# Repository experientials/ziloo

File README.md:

# Ziloo

Ziloo is an independent device that sees and senses the environment. It recognises objects and behavior based on what it has been taught. It outputs an event log describing what is perceived.
Ziloo can be placed on a shelf, wall or embedded. I will recognise things and people it has been trained to recognise. They have to appear in front within 20cm - 200cm. Ziloo is primarily used indoors and used at all times of the day.

It receives stereo video input over 2 x 2-lane MIPI CSI2. Additionally it receives sensor input over I2C
for distance, color, brightness. The sensor inputs are processed and disected to identify objects, people and
behaviour. Ziloo can connect over USB to make the output available.

Ziloo will be launched on Kickstarter in 2022.

TODO 3D Exploded assembly
https://www.fiverr.com/visual_pro022/3d-product-animation-3d-product-video-3d-animation-3d-product-animation?context_referrer=search_gigs&source=top-bar&ref_ctx_id=ea6e5c3e42e5d61ed2beb57da5dea006&pckg_id=1&pos=13&context_type=auto&funnel=ea6e5c3e42e5d61ed2beb57da5dea006

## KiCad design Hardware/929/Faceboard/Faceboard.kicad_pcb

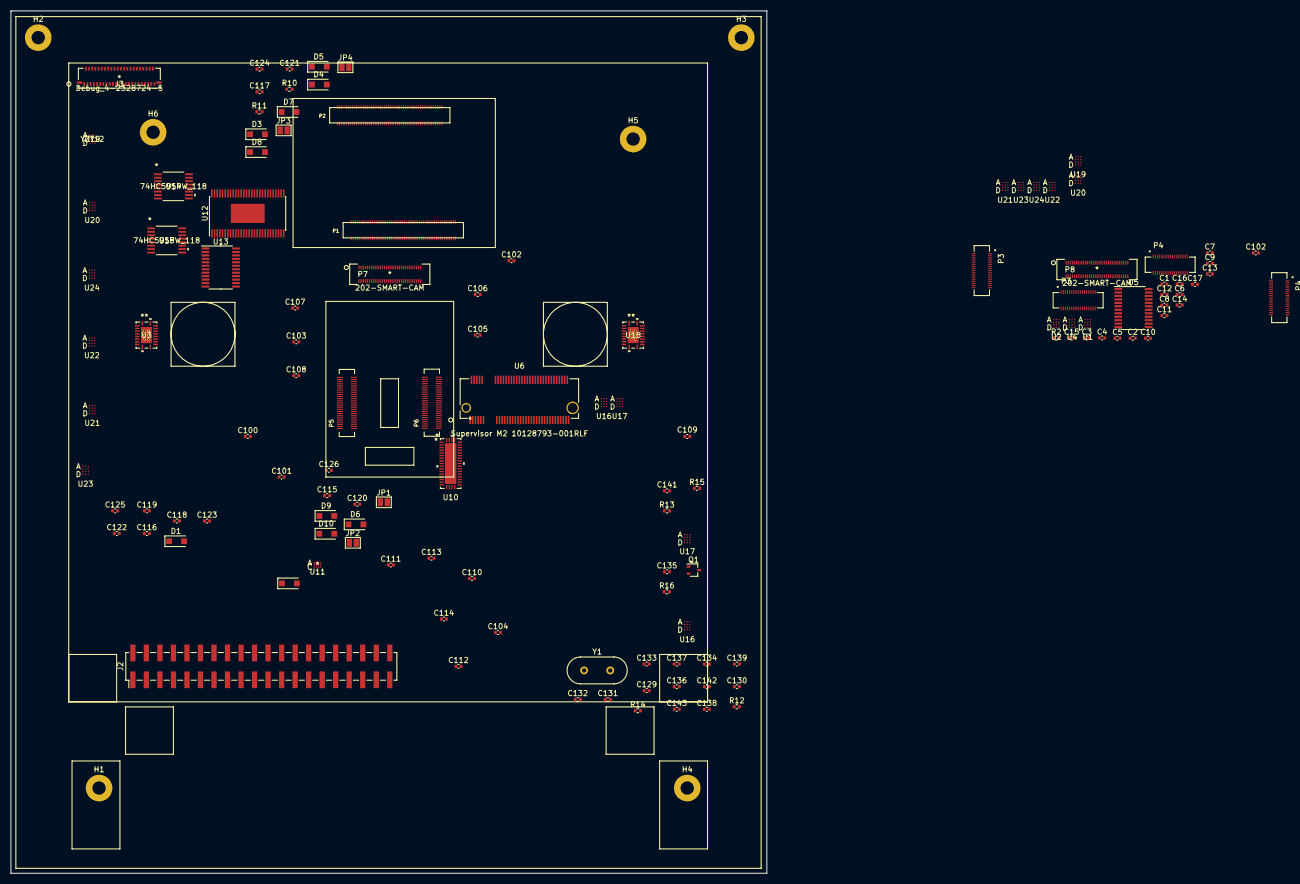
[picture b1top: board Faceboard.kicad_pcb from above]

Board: 4 copper layers, 142.0 x 162.0 mm, 130 parts (0 on the bottom side), 161 nets, no tracks yet.

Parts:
C1, C2, C6, C116, C121: 1uF; C_0402_1005Metric
C3, C4, C5, C7, C8, C9, C10, C11, C12, C13, C14, C15, C16, C17, C101, C102, C102#2, C103, C104, C105, C106, C107, C108, C109, C110, C111, C112, C113, C114, C115, C117, C118, C119, C120, C122, C123, C124, C125, C133, C134, C141, C142: 100nF; C_0402_1005Metric
C100: 10nF; C_0402_1005Metric
C126: CAP; C_0402_1005Metric
C129, C143: 27pF; C_0402_1005Metric
C130, C131, C137, C138, C139: 100uF; C_0402_1005Metric
C132, C136: 10uF; C_0402_1005Metric
C135: 100pF; C_0402_1005Metric
D1, D2, D3, D4, D5, D6, D7, D8, D9, D10: D_Schottky; D_SOD-123F
H1, H2, H3, H4, H5, H6: MountingHole; MountingHole_2.5mm_Pad
J2: Raspberry_Pi_to_Ziloo; PinHeader_2x20_P2.54mm_Vertical_SMD
J3: Debug_4-2328724-5; 4-2328724-5
JP1: TDO; SolderJumper-2_P1.3mm_Open_Pad1.0x1.5mm
JP2: TDI; SolderJumper-2_P1.3mm_Open_Pad1.0x1.5mm
JP3: SYS_SDA; SolderJumper-2_P1.3mm_Open_Pad1.0x1.5mm
JP4: SYS_SCL; SolderJumper-2_P1.3mm_Open_Pad1.0x1.5mm
P1: UCM-P1-100DS-0.4V; HRS_DF40C-100DS-0.4V(51)
P2: UCM-P2-100DS-0.4V; HRS_DF40C-100DS-0.4V(51)
P3, P3#2, P4, P4#2: 201-SOCKET-34DS-0.4V(51); HIROSE_DF40C-34DS-0.4V(51)
P5: T-USB_PWRCTL-50; HRS_DF40C-50DS-0.4V(51)
P6: T-USB_HIGH-SPEED-50; HRS_DF40C-50DS-0.4V(51)
P7, P8: 202-SMART-CAM; DF40C-60DS-0.4V51
Q1: 2SC4213; SOT-323_SC-70
R2, R10: 10K; R_0402_1005Metric
R11: R; R_0402_1005Metric
R12: 10k; R_0402_1005Metric
R13: 1k; R_0402_1005Metric
R14: 100K; R_0402_1005Metric
R15, R16: 4.7K; R_0402_1005Metric
U1, U2, U4, U16#2, U17, U19, U20#2, U21#2, U22#2, U23, U24: TXS0104; TXS0104EYZTR
U3, U18: SN74CB3Q3245RGYR
U5, U13: PCA9555PW; TSSOP-24_4.4x7.8mm_P0.65mm
U6: Supervisor M2 10128793-001RLF; 10128793-001RLF
U10: CBTL04083ABS_518
U11: TS5USBC410YFFR
U12: Faceboard_Expander_FR2032IG56; HTSSOP-56-1EP_6.1x14mm_P0.5mm_EP3.61x6.35mm
U14, U15: 74HC595PW_118; TSSOP-16
U16, U17#2, U19#2, U20, U21, U22, U23#2, U24#2: YZT12; TXS0104EYZTR
Y1: 25.000MHz; Crystal_HC18-U_Vertical

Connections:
+1V8: C9.1, C13.1, C15.1, C103.1, C105.1, C107.1, C109.1, C111.1, C113.1, C133.1, C141.1, P3.4 (VCC_1V8), P3#2.4 (VCC_1V8), P4.4 (VCC_1V8), P4#2.4 (VCC_1V8), P7.12 (1V8), P7.30 (1V8), U1.B1 (VCCB), U2.B1 (VCCB), U4.B1 (VCCB), U16#2.B1 (VCCB), U17.B1 (VCCB), U19.B1 (VCCB), U20#2.B1 (VCCB), U21#2.B1 (VCCB), U22#2.B1 (VCCB), U23.B1 (VCCB), U24.B1 (VCCB)
+2V8: P3.2 (AVDD_2V8), P3#2.2 (AVDD_2V8), P4.2 (AVDD_2V8), P4#2.2 (AVDD_2V8)
+3.3V: C1.2, C2.2, C3.2, C4.2, C5.2, C11.1, C14.1, C16.1, C17.2, C104.1, C106.1, C108.1, C110.1, C112.1, C114.1, C115.2, C121.2, C122.2, C123.2, C124.2, C125.2, C126.1, C130.1, C131.1, C132.1, C134.1, C136.1, C137.1, C138.1, C139.1, C142.1, J3.2, P7.6 (3V3), P7.24 (3V3), R2.1, R10.1, R11.1, R12.2, R13.2, R14.1, U1.B2 (VCCA), U2.B2 (VCCA), U3.20 (VCC), U4.B2 (VCCA), U5.24 (VDD), U6.2 (3V3), U6.70 (3V3), U6.72 (3V3), U6.74 (3V3), U10.5 (VDD), U10.8 (VDD), U10.13 (VDD), U10.18 (VDD), U10.20 (VDD), U10.30 (VDD), U10.40 (VDD), U10.42 (VDD), U11.B1 (VCC), U13.24 (VDD), U14.16 (VCC), U15.16 (VCC), U16#2.B2 (VCCA), U17.B2 (VCCA), U18.20 (VCC), U19.B2 (VCCA), U20#2.B2 (VCCA), U21#2.B2 (VCCA), U22#2.B2 (VCCA), U23.B2 (VCCA), U24.B2 (VCCA)
+VDC: D1.1 (K), D2.1 (K), D3.1 (K), D4.1 (K), D5.1 (K), D6.1 (K), D7.1 (K), D8.1 (K), D9.1 (K), D10.1 (K), P1.11 (V_SOM), P1.27 (V_SOM), P1.43 (V_SOM), P1.57 (V_SOM), P1.69 (V_SOM), P1.83 (V_SOM), P2.9 (V_SOM), P2.19 (V_SOM), P2.29 (V_SOM), P2.39 (V_SOM), P2.57 (V_SOM), P2.71 (V_SOM), P2.87 (V_SOM)
/Camera + Sound Domain/CSI1_CLK_N: P3#2.18 (CSI_RX_CLKN), P7.27 (LEFT_CSI_CLK-)
/Camera + Sound Domain/CSI1_CLK_P: P3#2.19 (CSI_RX_CLKP), P7.25 (LEFT_CSI_CLK+)
/Camera + Sound Domain/CSI1_D0_N: P3#2.27 (CSI_RX_D0N), P7.21 (LEFT_CSI0-)
/Camera + Sound Domain/CSI1_D0_P: P3#2.28 (CSI_RX_D0P), P7.19 (LEFT_CSI0+)
/Camera + Sound Domain/CSI1_D1_N: P3#2.24 (CSI_RX_D1N), P7.15 (LEFT_CSI1-)
/Camera + Sound Domain/CSI1_D1_P: P3#2.25 (CSI_RX_D1P), P7.13 (LEFT_CSI1+)
/Camera + Sound Domain/CSI1_D2_N: P3#2.21 (CSI_RX_D2N), P7.9 (LEFT_CSI2-)
/Camera + Sound Domain/CSI1_D2_P: P3#2.22 (CSI_RX_D2P), P7.7 (LEFT_CSI2+)
/Camera + Sound Domain/CSI2_CLK_N: P4.18 (CSI_RX_CLKN), P7.28 (RIGHT_CSI_CLK-)
/Camera + Sound Domain/CSI2_CLK_P: P4.19 (CSI_RX_CLKP), P7.26 (RIGHT_CSI_CLK+)
/Camera + Sound Domain/CSI2_D0_N: P4.27 (CSI_RX_D0N), P7.22 (RIGHT_CSI0-)
/Camera + Sound Domain/CSI2_D0_P: P4.28 (CSI_RX_D0P), P7.20 (RIGHT_CSI0+)
/Camera + Sound Domain/CSI2_D1_N: P4.24 (CSI_RX_D1N), P7.16 (RIGHT_CSI1-)
/Camera + Sound Domain/CSI2_D1_P: P4.25 (CSI_RX_D1P), P7.14 (RIGHT_CSI1+)
/Camera + Sound Domain/I2S_1V8_RXC: P3#2.14 (BCLK/SCK), P4.14 (BCLK/SCK), P7.54 (I2S_SCK), U19.A1
/Camera + Sound Domain/I2S_1V8_RXD1: P3#2.16 (SDATA1), P4.16 (SDATA1), P7.50 (I2S_D1), U19.A3
/Camera + Sound Domain/I2S_1V8_RXD2: P7.48 (I2S_D2), U19.D3 (A4)
/Camera + Sound Domain/I2S_1V8_RXFS: P3#2.15 (WS/LRCLK), P4.15 (WS/LRCLK), P7.52 (I2S_LRCLK), U19.A2
/Camera + Sound Domain/LEFT_SCL: P7.31 (LEFT_SCL), U23.C1 (B1)
/Camera + Sound Domain/LEFT_SDA: P7.33 (LEFT_SDA), U23.C2 (B2)
/Camera + Sound Domain/OE_CAM: P7.39 (OE_CAM), U22#2.B3 (OE), U23.B3 (OE), U24.B3 (OE)
/Camera + Sound Domain/OE_SOUND: P7.41 (OE_SOUND), U19.B3 (OE), U20#2.B3 (OE), U21#2.B3 (OE)
/Camera + Sound Domain/RIGHT_SCL: P7.32 (RIGHT_SCL), U23.C3 (B3)
/Camera + Sound Domain/RIGHT_SDA: P7.34 (RIGHT_SDA), U23.D1 (B4)
/Combi Camera/LEFT_ATT_INT: U2.C2 (B2), U5.15 (IO1_2)
/Combi Camera/LEFT_ATT_XSHUT: U2.C1 (B1), U5.16 (IO1_3)
/Combi Camera/LEFT_PWRDN: U2.D1 (B4), U5.13 (IO1_0)
/Combi Camera/LEFT_RESET: U2.C3 (B3), U5.14 (IO1_1)
/Combi Camera/LEFT_SCL: P8.31 (LEFT_SCL), U1.C1 (B1)
/Combi Camera/LEFT_SDA: P8.33 (LEFT_SDA), U1.C2 (B2)
/Combi Camera/RIGHT_ATT_INT: U4.C2 (B2), U5.19 (IO1_6)
/Combi Camera/RIGHT_ATT_XSHUT: U4.C1 (B1), U5.20 (IO1_7)
/Combi Camera/RIGHT_PWRDN: U4.D1 (B4), U5.17 (IO1_4)
/Combi Camera/RIGHT_RESET: U4.C3 (B3), U5.18 (IO1_5)
/Combi Camera/RIGHT_SCL: P8.32 (RIGHT_SCL), U1.C3 (B3)
/Combi Camera/RIGHT_SDA: P8.34 (RIGHT_SDA), U1.D1 (B4)
/Combi Camera/SENSOR_INT: P8.45 (SYS_EX_nINT), R2.2, U5.1 (~INT)
/Combi Camera/SYS_SCL: P8.42 (SYS_SCL), U5.22 (SCL)
/Combi Camera/SYS_SDA: P8.44 (SYS_SDA), U5.23 (SDA)
/Expander, M.2 and T-USB/ALT_BOOT: J3.19, P5.22 (ALT_BOOT), U12.10 (ALT_BOOT/P4.4)
/Expander, M.2 and T-USB/BOTH_VSOM: P5.11 (BOTH_VSOM), U12.39 (BOTH_VSOM/P2.3)
/Expander, M.2 and T-USB/B_PERST: U13.4 (IO0_0), U15.15 (Q0)
/Expander, M.2 and T-USB/FACE-EX_FW_RXD: P5.47 (UART1_RXD), U3.16 (B3), U12.27 (UART1_RX/UCA0SOMI/A1/Vref+/P1.1)
/Expander, M.2 and T-USB/FACE-EX_FW_TXD: P6.19 (STEM_INT), U3.15 (B4), U12.28 (STEM_INT/UCA0SIMO/A0/Vref-/P1.0)
/Expander, M.2 and T-USB/FACE_TCK: JP4.2 (B), U12.24 (SYS_SCL/TCK/A4/VREF+/P1.4)
/Expander, M.2 and T-USB/FACE_TDI: JP2.2 (B), U12.22 (TA0.2/TDI/TCLK/A6/P1.6)
/Expander, M.2 and T-USB/FACE_TDO: JP1.2 (B), U12.21 (TA0.1/TDO/A7/P1.7)
/Expander, M.2 and T-USB/FACE_TMS: JP3.2 (B), U12.23 (SYS_SDA/TMS/A5/P1.5)
/Expander, M.2 and T-USB/F_SBWTCK: U3.2 (A1), U3.18 (B1), U12.17 (TEST/SBWTCK)
/Expander, M.2 and T-USB/F_SBWTDIO: U3.3 (A2), U3.17 (B2), U12.16 (~RST/NMI/SBWTDIO)
/Expander, M.2 and T-USB/LEFT_ATT_XSHUT: J3.33, U13.16 (IO1_3)
/Expander, M.2 and T-USB/LEFT_PWRDN: J3.35, U13.13 (IO1_0)
/Expander, M.2 and T-USB/LEFT_RESET: J3.34, U13.14 (IO1_1)
/Expander, M.2 and T-USB/LVDS_DISP_RESET: U13.10 (IO0_6), U15.6 (Q6)
/Expander, M.2 and T-USB/LVDS_TOUCH_RESET: U13.11 (IO0_7), U15.7 (Q7)
/Expander, M.2 and T-USB/M2B_USB_MUX: U10.9 (SEL), U15.3 (Q3)
/Expander, M.2 and T-USB/M.2 Key B connector/B_PWROFF: R13.1, U6.6 (PWR_OFF)
/Expander, M.2 and T-USB/M.2 Key B connector/PCIE_CLGEN_X1: C143.1, Y1.1
/Expander, M.2 and T-USB/MCU_SYS_INT: P5.12 (MCU_SYS_INT), U12.25 (MCU_SYS_INT/A3/P1.3), U13.6 (IO0_2)
/Expander, M.2 and T-USB/PMIC_ON_REQ: P5.18 (PMIC_ON_REQ), U12.30 (PMIC_ON_REQ/P5.4)
/Expander, M.2 and T-USB/PMIC_STBY_REQ: P5.19 (PMIC_STBY_REQ), U12.29 (PMIC_STBY_REQ/P5.5)
/Expander, M.2 and T-USB/POR_B_3P3: P5.17 (POR_B_3P3), U12.40 (POR_B_3P3/P2.2)
/Expander, M.2 and T-USB/PWRBTN: J3.17, P5.21 (PWRBTN), U12.11 (PWRBTN/P4.3)
/Expander, M.2 and T-USB/RIGHT_ATT_XSHUT: J3.39, U13.20 (IO1_7)
/Expander, M.2 and T-USB/RIGHT_PWRDN: J3.41, U13.17 (IO1_4)
/Expander, M.2 and T-USB/RIGHT_RESET: J3.40, U13.18 (IO1_5)
/Expander, M.2 and T-USB/STEM_I2C_SCL: J3.44, P6.17 (STEM_SCL)
/Expander, M.2 and T-USB/STEM_I2C_SDA: J3.45, P6.18 (STEM_SDA)
/Expander, M.2 and T-USB/SYS_EX_nINT: R10.2, U13.1 (~INT)
/Expander, M.2 and T-USB/SYS_I2C_SCL: J3.42, JP4.1 (A), P5.13 (SYS_I2C_SCL), U13.22 (SCL)
/Expander, M.2 and T-USB/SYS_I2C_SDA: J3.43, JP3.1 (A), P5.14 (SYS_I2C_SDA), U13.23 (SDA)
/Expander, M.2 and T-USB/SYS_RST_PMIC: J3.16, P5.16 (SYS_RST_PMIC), U12.7 (SYS_RST_PMIC/P4.7)
/Expander, M.2 and T-USB/T-USB-EX_FW_RXD: P6.28 (UART_T_TXD), U3.12 (B7)
/Expander, M.2 and T-USB/T-USB-EX_FW_TXD: P6.27 (UART_T_RXD), U3.11 (B8)
/Expander, M.2 and T-USB/T-USB_SPI_CS: P5.33 (SPI_CS), U12.36 (P2.6)
/Expander, M.2 and T-USB/T_SBWTCK: P6.21 (T_SBWTCK), U3.6 (A5), U3.14 (B5)
/Expander, M.2 and T-USB/T_SBWTDIO: P6.23 (T_SBWTDIO), U3.7 (A6), U3.13 (B6)
/Expander, M.2 and T-USB/UART1_TXD: P5.48 (UART1_TXD), U12.26 (UART1_TX/A2/P1.2)
/Expander, M.2 and T-USB/UART2_RXD: P5.45 (UART2_RXD), P5.46 (UART2_TXD)
/UART1_RXD: P1.19 (UART1_RXD), P1.21 (UART3_RXD), P1.76 (UART2_RXD), P1.84 (UART4_RXD)
/UART1_TXD: P1.61 (UART3_TXD), P1.72 (UART1_TXD), P1.74 (UART2_TXD), P1.86 (UART4_TXD)
GND: C1.1, C2.1, C3.1, C4.1, C5.1, C6.1, C7.1, C8.1, C9.2, C10.1, C11.2, C12.1, C13.2, C14.2, C15.2, C16.2, C17.1, C100.2, C101.2, C102.1, C102#2.1, C103.2, C104.2, C105.2, C106.2, C107.2, C108.2, C109.2, C110.2, C111.2, C112.2, C113.2, C114.2, C115.1, C116.1, C117.1, C118.1, C119.1, C120.1, C121.1, C122.1, C123.1, C124.1, C125.1, C126.2, C129.2, C130.2, C131.2, C132.2, C133.2, C134.2, C135.2, C136.2, C137.2, C138.2, C139.2, C141.2, C142.2, C143.2, J3.4, J3.7, J3.10, P1.4 (GND), P1.10 (GND), P1.20 (GND), P1.40 (GND), P1.54 (GND), P1.64 (GND), P1.78 (GND), P1.88 (GND), P2.10 (GND), P2.16 (GND), P2.22 (GND), P2.28 (GND), P2.34 (GND), P2.40 (GND), P2.46 (GND), P2.54 (GND), P2.72 (GND), P2.82 (GND), P3.5 (GND), P3.20 (GND), P3.23 (GND), P3.26 (GND), P3.29 (GND), P3.34 (AGND), P3#2.5 (GND), P3#2.20 (GND), P3#2.23 (GND), P3#2.26 (GND), P3#2.29 (GND), P3#2.34 (AGND), P4.5 (GND), P4.20 (GND), P4.23 (GND), P4.26 (GND), P4.29 (GND), P4.34 (AGND), P4#2.5 (GND), P4#2.20 (GND), P4#2.23 (GND), P4#2.26 (GND), P4#2.29 (GND), P4#2.34 (AGND), P5.2 (GND), P5.5 (GND), P5.8 (GND), P5.49 (GND), P6.4 (GND), P6.7 (GND), P6.10 (GND), P6.13 (GND), P6.20 (GND), P6.33 (GND), P8.5 (GND), P8.11 (GND), P8.17 (GND), P8.23 (GND), P8.29 (GND), Q1.2 (E), R16.2, U1.D2 (GND), U2.D2 (GND), U3.10 (GND), U4.D2 (GND), U5.12 (VSS), U6.3 (GND), U6.5 (GND), U6.27 (GND), U6.33 (GND), U6.39 (GND), U6.45 (GND), U6.51 (GND), U6.57 (GND), U10.1 (GND), U10.4 (GND), U10.10 (GND), U10.21 (GND), U10.39 (GND), U10.41 (XSD01), U10.43 (GND), U11.B3 (GND), U11.B4 (OE), U12.14 (DVSS), U13.12 (VSS), U14.8 (GND), U15.8 (GND), U16#2.D2 (GND), U17.D2 (GND), U18.10 (GND), U19.D2 (GND), U20#2.D2 (GND), U21#2.D2 (GND), U22#2.D2 (GND), U23.D2 (GND), U24.D2 (GND), Y1.2
unnamed: C6.2, C7.2, C8.2, C10.2, C12.2
unnamed: C100.1, C101.1, P1.62 (UCM_AVDD33_ETH)
unnamed: C102.2, C102#2.2, P1.55 (PHY_2V5_OUT)
unnamed: C116.2, C117.2, C118.2, C119.2, C120.2
unnamed: C135.1, Q1.3 (C), R14.2, U6.67 (RESET)
unnamed: D1.2 (A), P6.48 (VSOM)
unnamed: D2.2 (A), P6.45 (VSOM)
unnamed: D3.2 (A), P6.42 (VSOM)
unnamed: D4.2 (A), P6.39 (VSOM)
unnamed: D5.2 (A), P6.36 (VSOM)
unnamed: D6.2 (A), P6.26 (VSOM)
unnamed: D7.2 (A), P6.1 (VSOM)
unnamed: D8.2 (A), P5.15 (VSOM_LOCK), U12.19 (TA1.2/P8.3)
unnamed: D9.2 (A), P5.1 (VSOM)
unnamed: D10.2 (A), P5.26 (VSOM), U12.18 (TA1.1/P4.0)
unnamed: P3.9 (ATT_INT), P3#2.9 (ATT_INT), U2.A2, U24.A1
unnamed: P3.10 (ATT_XSHUT), P3#2.10 (ATT_XSHUT), U2.A1, U24.A2
unnamed: P3.12 (I2C_SCL), P3#2.12 (I2C_SCL), U1.A1, U23.A1
unnamed: P3.13 (I2C_SDA), P3#2.13 (I2C_SDA), U1.A2, U23.A2
unnamed: P3.18 (CSI_RX_CLKN), P8.27 (LEFT_CSI_CLK-)
unnamed: P3.19 (CSI_RX_CLKP), P8.25 (LEFT_CSI_CLK+)
unnamed: P3.21 (CSI_RX_D2N), P8.9 (LEFT_CSI2-)
unnamed: P3.22 (CSI_RX_D2P), P8.7 (LEFT_CSI2+)
unnamed: P3.24 (CSI_RX_D1N), P8.15 (LEFT_CSI1-)
unnamed: P3.25 (CSI_RX_D1P), P8.13 (LEFT_CSI1+)
unnamed: P3.27 (CSI_RX_D0N), P8.21 (LEFT_CSI0-)
unnamed: P3.28 (CSI_RX_D0P), P8.19 (LEFT_CSI0+)
unnamed: P3.32 (PWRDN), P3#2.32 (PWRDN), U2.D3 (A4), U24.D3 (A4)
unnamed: P3.33 (RESET), P3#2.33 (RESET), U2.A3, U24.A3
unnamed: P4.9 (ATT_INT), P4#2.9 (ATT_INT), U4.A2, U22#2.A1
unnamed: P4.10 (ATT_XSHUT), P4#2.10 (ATT_XSHUT), U4.A1, U22#2.A2
unnamed: P4.12 (I2C_SCL), P4#2.12 (I2C_SCL), U1.A3, U23.A3
unnamed: P4.13 (I2C_SDA), P4#2.13 (I2C_SDA), U1.D3 (A4), U23.D3 (A4)
unnamed: P4#2.18 (CSI_RX_CLKN), P8.28 (RIGHT_CSI_CLK-)
unnamed: P4#2.19 (CSI_RX_CLKP), P8.26 (RIGHT_CSI_CLK+)
unnamed: P4#2.24 (CSI_RX_D1N), P8.16 (RIGHT_CSI1-)
unnamed: P4#2.25 (CSI_RX_D1P), P8.14 (RIGHT_CSI1+)
unnamed: P4#2.27 (CSI_RX_D0N), P8.22 (RIGHT_CSI0-)
unnamed: P4#2.28 (CSI_RX_D0P), P8.20 (RIGHT_CSI0+)
unnamed: P4.32 (PWRDN), P4#2.32 (PWRDN), U4.D3 (A4), U22#2.D3 (A4)
unnamed: P4.33 (RESET), P4#2.33 (RESET), U4.A3, U22#2.A3
unnamed: P5.6 (USB2_DP), U11.C3 (D1+)
unnamed: P5.7 (USB2_DN), U11.C4 (D1-)
unnamed: P6.8 (USB2_RX_DP), U10.38 (B0_P)
unnamed: P6.9 (USB2_RX_DN), U10.37 (B0_N)
unnamed: P6.11 (USB2_TX_DP), U10.36 (B1_P)
unnamed: P6.12 (USB2_TX_DN), U10.35 (B1_N)
unnamed: P7.5 (GND), P7.11 (GND), P7.17 (GND), P7.18 (GND), P7.23 (GND), P7.29 (GND), P7.56 (GND)
unnamed: P8.39 (OE_CAM), U1.B3 (OE), U2.B3 (OE), U4.B3 (OE)
unnamed: Q1.1 (B), R15.2, R16.1
unnamed: R11.2, U10.19 (XSD23)
unnamed: R12.1, U6.8 (W_DISABL1)
unnamed: U11.A1 (SEL1), U11.B2 (SEL2)
unnamed: U12.51 (SH2_STCP/P3.5), U15.12 (STCP)
unnamed: U12.52 (SH1_STCP/P3.4), U14.12 (STCP)
unnamed: U12.53 (SH_MR/P3.3), U14.10 (MR), U15.10 (MR)
unnamed: U12.54 (SH_SHCP/P3.2), U14.11 (SHCP), U15.11 (SHCP)
unnamed: U12.55 (SH_DS/P3.1), U14.14 (DS)
unnamed: U14.9 (Q7S), U15.14 (DS)
unnamed: U6.48 (GPIO_4), U16#2.A1
unnamed: U6.60 (COEX3), U16#2.A2
unnamed: U6.62 (M2B_UART_TXD), U16#2.A3
unnamed: U6.64 (M2B_UART_RXD), U16#2.D3 (A4)
unnamed: U6.40 (STEM_SCL), U17.A1
unnamed: U6.42 (STEM_SDA), U17.A2
unnamed: U6.44 (GNSS_IRQ), U17.A3
unnamed: U6.46 (GPIO_3), U17.D3 (A4)
unnamed: U6.56 (MFG_DAT), U18.11 (B8)
unnamed: U6.58 (MFG_CLK), U18.12 (B7)
unnamed: U6.66 (DETECT/CMD), U18.13 (B6)
unnamed: U6.68 (SUSCLK/SDCLK), U18.14 (B5)
unnamed: U6.65 (SD2_DATA3), U18.15 (B4)
unnamed: U6.63 (SD2_DATA2), U18.16 (B3)
unnamed: U6.61 (SD2_DATA1), U18.17 (B2)
unnamed: U6.59 (SD2_DATA0), U18.18 (B1)

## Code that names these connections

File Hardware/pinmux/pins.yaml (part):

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  P20.17: {som: P2.70, func: SD1_CMD, dest: "SD1", pad: ENET_MDIO, alts: [SAI6_TX_SYNC, I2C5_SDA], tags: [sd, sd1]}
  P20.18: {som: P2.88, func: COEX, dest: "M.2 Key B", pad: ENET_INT, tags: [m2, m2keyb]}
  P20.19: {som: P2.53, func: SAI5_TXFS, dest: "Sound p4", pad: ENET_RX_CTL, alts: [SAI7_TX_SYNC], verified: measured, tags: [audio, sai5, speaker, lrclk, sound, measured]}
  P20.20: {som: P2.67, func: MCU_SYS_INT, dest: "Supervisor", pad: ENET_TX_CTL, alts: [SAI6_MCLK], tags: [gpio, int, supervisor]}
  P20.21: {som: P2.41, func: SD1_DATA2, dest: "SD1", pad: ENET_RD0, alts: [I2C4_SCL, SAI7_RX_DATA0], tags: [sd, sd1, data]}
  P20.22: {som: P2.59, func: SD1_DATA1, dest: "SD1", pad: ENET_TD0, alts: [SAI6_RX_BCLK], tags: [sd, sd1, data]}
  P20.23: {som: P2.43, func: SD1_DATA3, dest: "SD1", pad: ENET_RD1, alts: [I2C4_SDA, SAI7_RX_SYNC], tags: [sd, sd1, data]}
  P20.24: {som: P2.61, func: SD1_DATA0, dest: "SD1", pad: ENET_TD1, alts: [SAI6_RX_SYNC], tags: [sd, sd1, data]}
  P20.25: {som: P2.45, func: OE_SOUND, dest: "Sound (bus enable)", pad: ENET_RD2, alts: [SAI7_RX_BCLK], tags: [gpio, enable, sound]}
  P20.26: {som: P2.63, func: SAI5_TXD2, dest: "Sound p7", pad: ENET_TD2, alts: [SAI6_RX_DATA0], tags: [audio, sai5, speaker, data, sound]}
  P20.27: {som: P2.47, func: OE_CAM, dest: "Camera (bus enable)", pad: ENET_RD3, alts: [SAI7_MCLK], tags: [gpio, enable, camera]}
  P20.28: {som: P2.65, func: SAI5_TXD3, dest: "Sound p8", pad: ENET_TD3, alts: [SAI6_TX_BCLK], tags: [audio, sai5, speaker, data, sound]}
  P20.29: {som: P2.55, func: SAI5_TXC, dest: "Sound p3", pad: ENET_RXC, alts: [SAI7_TX_BCLK], tags: [audio, sai5, speaker, bclk, sound]}
  P20.30: {som: P2.69, func: SYS_PRG#, dest: "Supervisor", pad: ENET_TXC, alts: [SAI7_TX_DATA0], tags: [gpio, prog, supervisor]}
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
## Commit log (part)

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2021-10-19 Hardware plan
2021-10-20 Camera module connected
2021-10-27 Plan for module
2021-10-30 Camera module further
    - M12 lenses as option
    - Connector orientation
    - Current orientation RPi camera connectors
    - Design files for Module v1
2021-11-04 Split camera module in 2 designs
2021-11-04 Revision
2021-11-20 Lens testing plan
    * 3D models for testing hardware
    * Lens tech specs
    * Holder tech specs
2021-12-05 Datasheets: i.MX and USB
2021-12-05 Pin Allocations
2021-12-10 USB connector plans
2021-12-11 909 Brige Board
2021-12-12 Revised power connector
    - Camera Module Breakout pins
    - Board Power Connector as plain header througholes
2021-12-12 Battery Power board
    With revisions from implentation and v1 notes
2021-12-14 909 readme & older power design
2021-12-21 Model 909b
2021-12-28 Two alt breakout connectors
2022-01-09 Broken into milestones
2022-01-09 More datasheets
2022-01-10 Final 909b design
    - Debug muxing of USB 2.0
    - T-USB Alt. Modes
    - Pins on drawings
2022-01-19 I2C/I2S connector tweaks
2022-02-13 More Expansions
    - Audio SAI5 in/out update
    - 40 pin GPIO Header
2022-02-15 Capture pin allocations
2022-02-16 Using CBTL04083 mux instead of HD3SS3220
    + Interrupts
    + Clarified audio pins and I2C/I2S breakout connectors
2022-02-21 Power datasheets re-org
2022-03-01 T-USB board
2022-03-01 Refined Testing Board breakouts
2022-03-08 Finalising T-USB board
2022-03-26 Smiley front prototype
2022-05-16 909c update with Power Module
2022-05-21 T-USB update
    Testing board goes down below
    Horizontal spaced connectors around USB T
    Drawings
2022-05-21 919 readme
2022-05-25 i.MX 8 refs
2022-06-13 919 two stages of design plan
2022-06-13 T-USB and STEM
2022-06-15 Revised USB 2.0 muxing
2022-06-15 I2C adresses
2022-06-17 Moved camera designs to 201
2022-06-22 Clarifications T-USB and 909c
    - Updated 909c with T-USB daughterboard
    - Updated T-USB Power Module
2022-07-13 201 module testing
2022-07-13 Connectivity
    - Connecting to Host PC/UI
    - Using GPIO to build stuff
    - The Activity State of the board
2022-07-19 Decor and Layout on Smiley
2022-07-30 Test Board schematic
    * EX0_nINT -> SYS_nINT. EX_T_nINT to STEM_INT.
    * Revised Breakout connectors
    * Reintroduced MCU_SYS_INT pin on 50 pins connector.
    * Spec updated with pinouts and new connectors
    * 3D design update
    * Testing Board doc update and I2C address corrections
2022-07-30 T-USB Altium schemas
2022-08-03 Stem Expander
    Replacing PCA9555 with MCP430
2022-08-05 MSP debug pins tweaks
2022-08-11 M.2 reference update
2022-08-13 Key B pinout revision
2022-08-21 SoM Pin connections
    - Backwards compatible interrupt pin now named SYS_nINT
    - SOUND_INT, COEX3
    - Corrected I2S connections
    - Assigned STEM_INT to GPIO1_1
2022-08-23 The Stem definition
    - KiCad lib is in separate repo
    - 919 expansion document
    - Additional datasheets
2022-08-24 KiCAD designs for testing
2022-08-31 Updated I/O Expander plans
2022-08-31 202 combi camera board
2022-08-31 Bob 929

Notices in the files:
parts and their libraries:
Copyright 2021 Accelerated Designs. All rights reserved.
